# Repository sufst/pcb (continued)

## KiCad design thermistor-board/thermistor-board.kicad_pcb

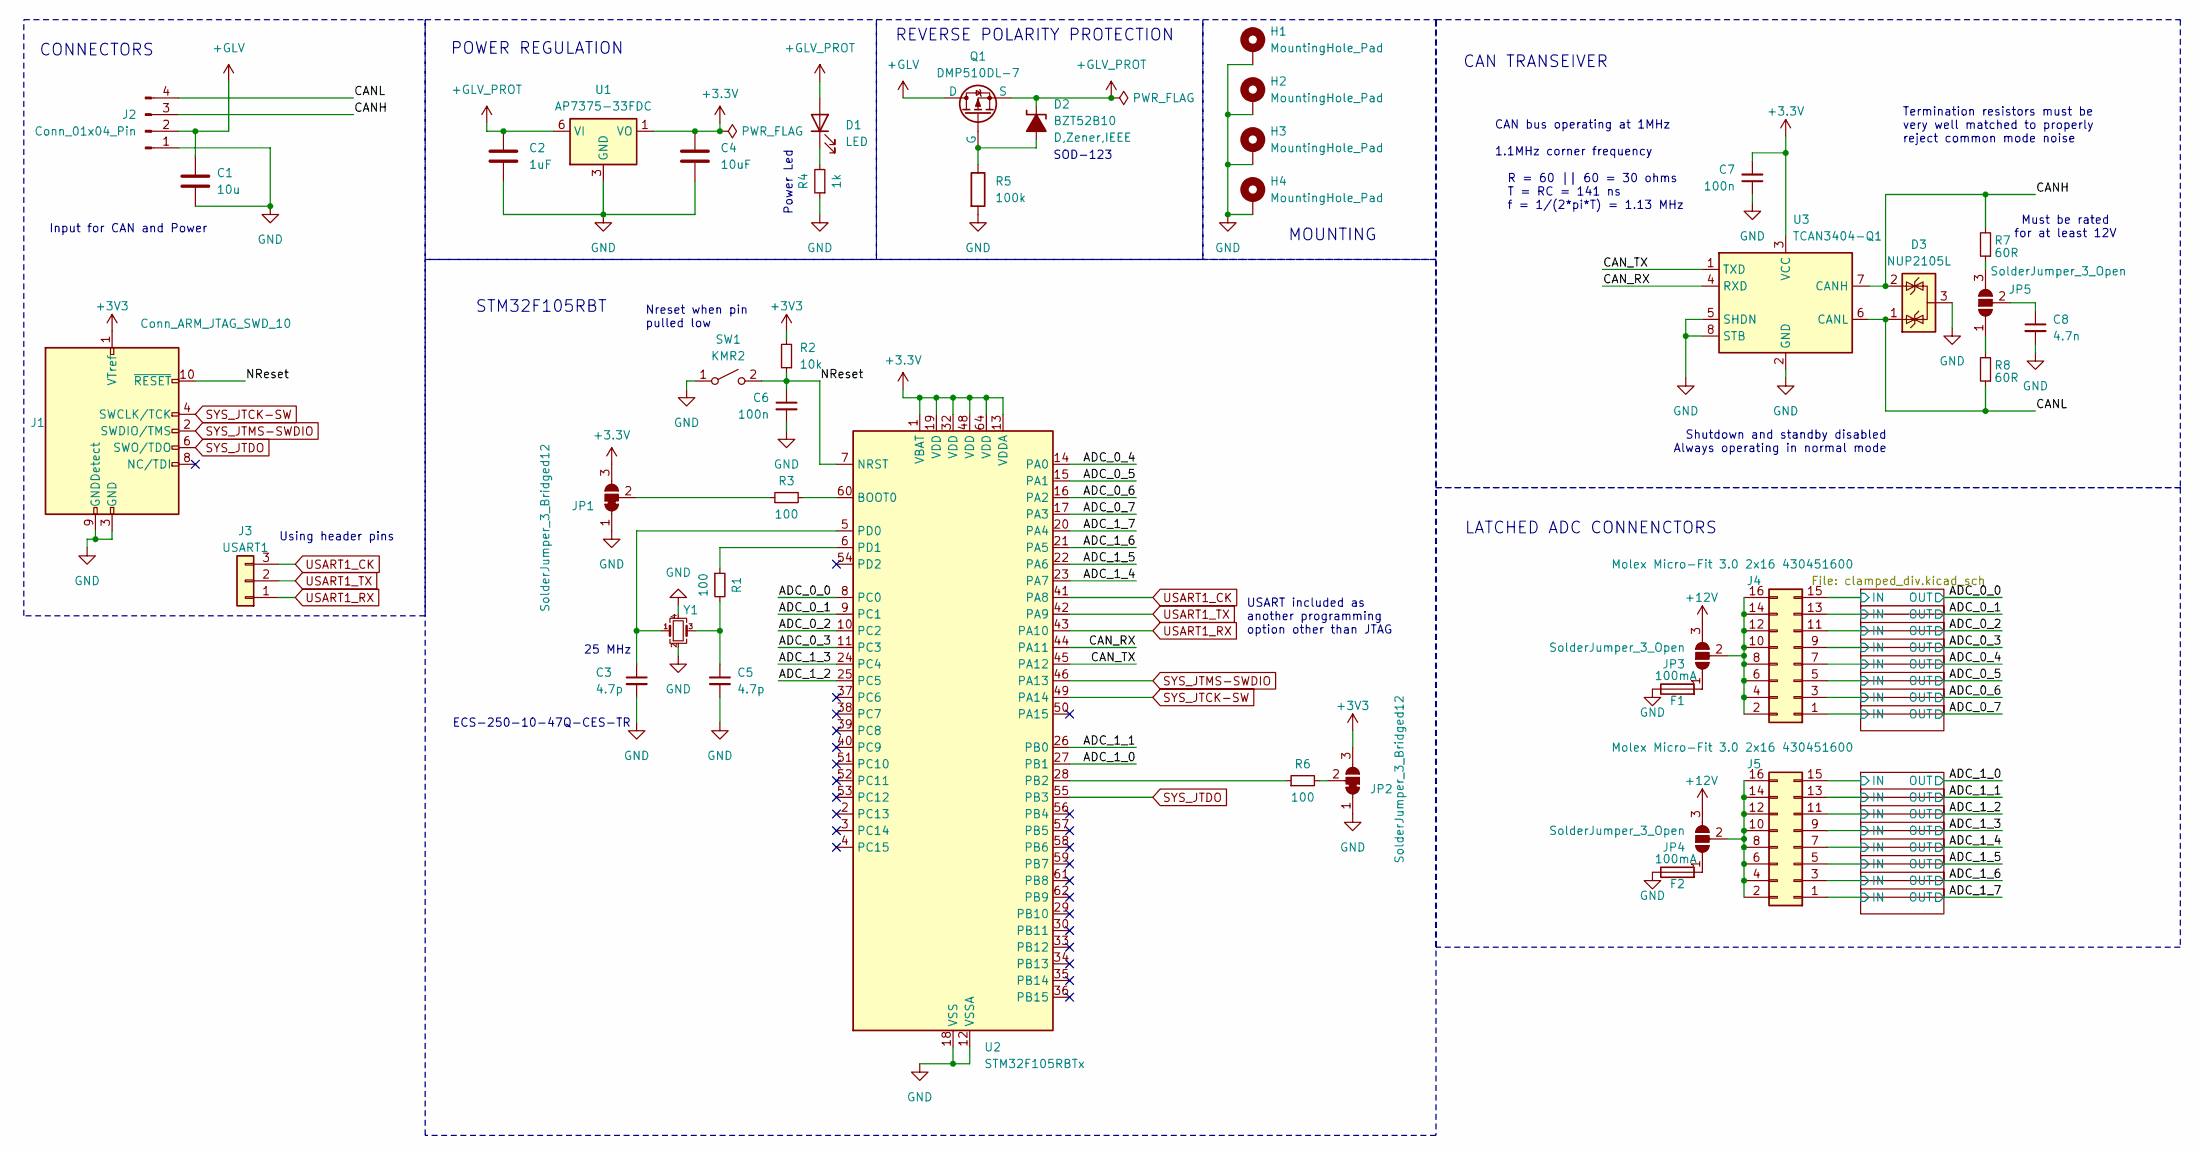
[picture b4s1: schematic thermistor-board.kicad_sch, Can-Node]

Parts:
C1: 10u; C_0805_2012Metric_Pad1.18x1.45mm_HandSolder
C2: 1uF; C_0805_2012Metric_Pad1.18x1.45mm_HandSolder
C3, C5: 4.7p; C_0603_1608Metric_Pad1.08x0.95mm_HandSolder
C4: 10uF; C_0805_2012Metric_Pad1.18x1.45mm_HandSolder
C6, C7: 100n; C_0603_1608Metric_Pad1.08x0.95mm_HandSolder
C8: 4.7n; C_0603_1608Metric_Pad1.08x0.95mm_HandSolder
D1: LED; LED_0805_2012Metric_Pad1.15x1.40mm_HandSolder
D2: BZT52B10; D_SOD-123; MPN BZT52B10
D3: NUP2105L; SOT-23; MPN NUP2105L
F1, F2: 100mA; Fuse_0805_2012Metric_Pad1.15x1.40mm_HandSolder
H1, H2, H3, H4: MountingHole_Pad; MountingHole_3.2mm_M3_Pad_Via
J1: Conn_ARM_JTAG_SWD_10; SHF10501LDSMLC; MPN SHF-105-01-L-D-SM-LC
J2: Conn_01x04_Pin; Molex_Micro-Fit_3.0_43045-0400_2x02_P3.00mm_Horizontal
J3: USART1; PinHeader_1x03_P2.54mm_Vertical
J4, J5: Molex Micro-Fit 3.0 2x16 430451600
JP1, JP2: SolderJumper_3_Bridged12; SolderJumper-3_P1.3mm_Bridged12_RoundedPad1.0x1.5mm
JP3, JP4, JP5: SolderJumper_3_Open; SolderJumper-3_P1.3mm_Open_RoundedPad1.0x1.5mm
Q1: DMP510DL-7; SOT-23; MPN DMP510DL-7
R1, R3, R6: 100; R_0603_1608Metric_Pad0.98x0.95mm_HandSolder
R2: 10k; R_0603_1608Metric_Pad0.98x0.95mm_HandSolder
R4: 1k; R_0603_1608Metric_Pad0.98x0.95mm_HandSolder
R5: 100k; R_0805_2012Metric_Pad1.20x1.40mm_HandSolder
R7, R8: 60R; R_0603_1608Metric_Pad0.98x0.95mm_HandSolder
SW1: KMR2; SW_Push_1P1T_NO_CK_KMR2; MPN KMR221NG LFS
U1: AP7375-33FDC; DFN-6-1EP_2x2mm_P0.65mm_EP1.01x1.7mm
U2: STM32F105RBTx; LQFP-64_10x10mm_P0.5mm
U3: TCAN3404-Q1; SOT-23-8_Handsoldering; MPN TCAN3404DDFRQ1
Y1: ECS-250-10-47Q-CES-TR; Resonator_SMD_ECS_ECX-1247Q_1.6x1.2x0.3mm; MPN ECS-250-10-47Q-CES-TR

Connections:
+3.3V: C4.1, C7.2, JP1.3 (B), U1.1 (VO), U2.1 (VBAT), U2.13 (VDDA), U2.19 (VDD), U2.32 (VDD), U2.48 (VDD), U2.64 (VDD), U3.3 (VCC)
+3V3: J1.1 (VTref), JP2.3 (B), R2.2
+12V: JP3.3 (B), JP4.3 (B)
+GLV: C1.1, J2.2, Q1.1 (D)
+GLV_PROT: C2.1, D1.2 (A), D2.1 (K-), Q1.3 (S), U1.6 (VI)
/ADC_0_0: U2.8 (PC0); also elsewhere on the board
/ADC_0_1: U2.9 (PC1); also elsewhere on the board
/ADC_0_2: U2.10 (PC2); also elsewhere on the board
/ADC_0_3: U2.11 (PC3); also elsewhere on the board
/ADC_0_4: U2.14 (PA0); also elsewhere on the board
/ADC_0_5: U2.15 (PA1); also elsewhere on the board
/ADC_0_6: U2.16 (PA2); also elsewhere on the board
/ADC_0_7: U2.17 (PA3); also elsewhere on the board
/ADC_1_0: U2.27 (PB1); also elsewhere on the board
/ADC_1_1: U2.26 (PB0); also elsewhere on the board
/ADC_1_2: U2.25 (PC5); also elsewhere on the board
/ADC_1_3: U2.24 (PC4); also elsewhere on the board
/ADC_1_4: U2.23 (PA7); also elsewhere on the board
/ADC_1_5: U2.22 (PA6); also elsewhere on the board
/ADC_1_6: U2.21 (PA5); also elsewhere on the board
/ADC_1_7: U2.20 (PA4); also elsewhere on the board
/CANH: D3.2 (K), J2.3, R7.2, U3.7 (CANH)
/CANL: D3.1 (K), J2.4, R8.1, U3.6 (CANL)
/CAN_RX: U2.44 (PA11), U3.4 (RXD)
/CAN_TX: U2.45 (PA12), U3.1 (TXD)
/NReset: C6.1, J1.10 (~RESET), R2.1, SW1.2 (B), U2.7 (NRST)
GND: C1.2, C2.2, C3.2, C4.2, C5.2, C6.2, C7.1, C8.2, D3.3 (A), F1.1, F2.1, H1.1, H2.1, H3.1, H4.1, J1.3 (GND), J1.5 (GND), J1.9 (GNDDetect), J2.1, JP1.1 (A), JP2.1 (A), R4.1, R5.2, SW1.1 (A), U1.3 (GND), U1.7 (GND), U2.12 (VSSA), U2.18 (VSS), U2.31 (VSS), U2.47 (VSS), U2.63 (VSS), U3.2 (GND), U3.5 (SHDN), U3.8 (STB), Y1.2, Y1.4; also elsewhere on the board
unnamed: C5.1, R1.2, Y1.3
unnamed: D1.1 (K), R4.2
unnamed: D2.2 (A+), Q1.2 (G), R5.1
unnamed: J4.2, J4.4, J4.6, J4.8, J4.10, J4.12, J4.14, J4.16, JP3.2 (C)
unnamed: J5.2, J5.4, J5.6, J5.8, J5.10, J5.12, J5.14, J5.16, JP4.2 (C)
unnamed: JP1.2 (C), R3.1
unnamed: JP2.2 (C), R6.2
unnamed: F1.2, JP3.1 (A)
unnamed: F2.2, JP4.1 (A)
unnamed: JP5.1 (A), R8.2
unnamed: JP5.3 (B), R7.1
unnamed: C8.1, JP5.2 (C)
unnamed: R3.2, U2.60 (BOOT0)
unnamed: R6.1, U2.28 (PB2)
unnamed: C3.1, U2.5 (PD0), Y1.1
unnamed: R1.1, U2.6 (PD1)
SYS_JTCK-SW: J1.4 (SWCLK/TCK), U2.49 (PA14)
SYS_JTDO: J1.6 (SWO/TDO), U2.55 (PB3)
SYS_JTMS-SWDIO: J1.2 (SWDIO/TMS), U2.46 (PA13)
USART1_CK: J3.3, U2.41 (PA8)
USART1_RX: J3.1, U2.43 (PA10)
USART1_TX: J3.2, U2.42 (PA9)

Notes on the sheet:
REVERSE POLARITY PROTECTION
Must be rated for at least 12V
25 MHz
STM32F105RBT
LATCHED ADC CONNENCTORS
Input for CAN and Power
CONNECTORS
CAN TRANSEIVER
SOD-123
Nreset when pin pulled low
Shutdown and standby disabled Always operating in normal mode
ECS-250-10-47Q-CES-TR
Power Led
CAN bus operating at 1MHz 1.1MHz corner frequency R = 60 || 60 = 30 ohms T = RC = 141 ns f = 1/(2*pi*T) = 1.13 MHz
POWER REGULATION
Using header pins
Termination resistors must be very well matched to properly reject common mode noise
USART included as another programming option other than JTAG
MOUNTING

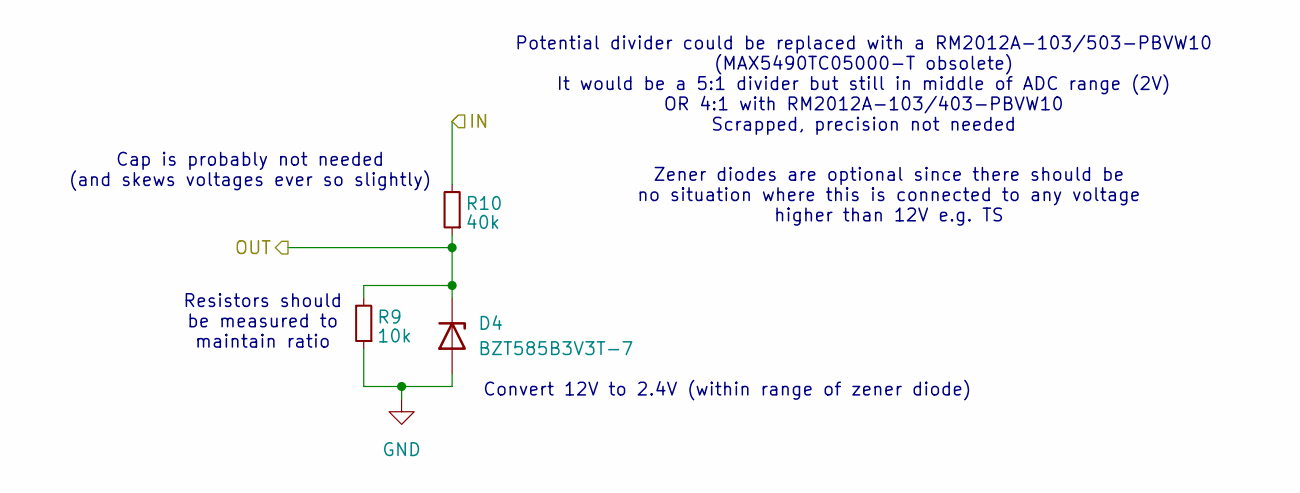
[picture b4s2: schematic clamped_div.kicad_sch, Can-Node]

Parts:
D4: BZT585B3V3T-7; D_SOD-523; Mouser Part Number 621-BZT585B3V3T-7
R9: 10k; R_0805_2012Metric_Pad1.20x1.40mm_HandSolder; Manufacturer_Part_Number CRGH0805F12R; Mouser Part Number 279-CRGH0805F12R
R10: 40k; R_0805_2012Metric_Pad1.20x1.40mm_HandSolder; Manufacturer_Part_Number CRCW080540K0FKEA; Mouser Part Number 71-CRCW080540K0FKEA

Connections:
/ADC_1_7: D4.1 (K), R9.2, R10.1; also elsewhere on the board
/ClampedDivider15/IN: R10.2
GND: D4.2 (A), R9.1; also elsewhere on the board

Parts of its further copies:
D5, D6, D7, D8, D9, D10, D11, D12, D13, D14, D15, D16, D17, D18, D19: BZT585B3V3T-7; D_SOD-523; Mouser Part Number 621-BZT585B3V3T-7
R11, R13, R15, R17, R19, R21, R23, R25, R27, R29, R31, R33, R35, R37, R39: 10k; R_0805_2012Metric_Pad1.20x1.40mm_HandSolder; Manufacturer_Part_Number CRGH0805F12R; Mouser Part Number 279-CRGH0805F12R
R12, R14, R16, R18, R20, R22, R24, R26, R28, R30, R32, R34, R36, R38, R40: 40k; R_0805_2012Metric_Pad1.20x1.40mm_HandSolder; Manufacturer_Part_Number CRCW080540K0FKEA; Mouser Part Number 71-CRCW080540K0FKEA

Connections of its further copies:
/ADC_0_0: D5.1 (K), R11.2, R12.1; also elsewhere on the board
/ADC_0_1: D17.1 (K), R35.2, R36.1; also elsewhere on the board
/ADC_0_2: D19.1 (K), R39.2, R40.1; also elsewhere on the board
/ADC_0_3: D18.1 (K), R37.2, R38.1; also elsewhere on the board
/ADC_0_4: D16.1 (K), R33.2, R34.1; also elsewhere on the board
/ADC_0_5: D15.1 (K), R31.2, R32.1; also elsewhere on the board
/ADC_0_6: D14.1 (K), R29.2, R30.1; also elsewhere on the board
/ADC_0_7: D13.1 (K), R27.2, R28.1; also elsewhere on the board
/ADC_1_0: D12.1 (K), R25.2, R26.1; also elsewhere on the board
/ADC_1_1: D11.1 (K), R23.2, R24.1; also elsewhere on the board
/ADC_1_2: D10.1 (K), R21.2, R22.1; also elsewhere on the board
/ADC_1_3: D9.1 (K), R19.2, R20.1; also elsewhere on the board
/ADC_1_4: D8.1 (K), R17.2, R18.1; also elsewhere on the board
/ADC_1_5: D7.1 (K), R15.2, R16.1; also elsewhere on the board
/ADC_1_6: D6.1 (K), R13.2, R14.1; also elsewhere on the board
/ClampedDivider16/IN: R12.2
/ClampedDivider17/IN: R14.2
/ClampedDivider18/IN: R16.2
/ClampedDivider19/IN: R18.2
/ClampedDivider20/IN: R20.2
/ClampedDivider21/IN: R22.2
/ClampedDivider22/IN: R24.2
/ClampedDivider23/IN: R26.2
/ClampedDivider24/IN: R28.2
/ClampedDivider25/IN: R30.2
/ClampedDivider26/IN: R32.2
/ClampedDivider27/IN: R34.2
/ClampedDivider28/IN: R36.2
/ClampedDivider29/IN: R38.2
/ClampedDivider30/IN: R40.2
GND: D5.2 (A), D6.2 (A), D7.2 (A), D8.2 (A), D9.2 (A), D10.2 (A), D11.2 (A), D12.2 (A), D13.2 (A), D14.2 (A), D15.2 (A), D16.2 (A), D17.2 (A), D18.2 (A), D19.2 (A), R11.1, R13.1, R15.1, R17.1, R19.1, R21.1, R23.1, R25.1, R27.1, R29.1, R31.1, R33.1, R35.1, R37.1, R39.1; also elsewhere on the board

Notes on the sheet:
Cap is probably not needed (and skews voltages ever so slightly)
Convert 12V to 2.4V (within range of zener diode)
Zener diodes are optional since there should be no situation where this is connected to any voltage higher than 12V e.g. TS
Resistors should be measured to maintain ratio
Potential divider could be replaced with a RM2012A-103/503-PBVW10 (MAX5490TC05000-T obsolete) It would be a 5:1 divider but still in middle of ADC range (2V) OR 4:1 with RM2012A-103/403-PBVW10 Scrapped, precision not needed

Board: 4 copper layers, 85 parts (0 on the bottom side), 44 nets, no tracks yet.

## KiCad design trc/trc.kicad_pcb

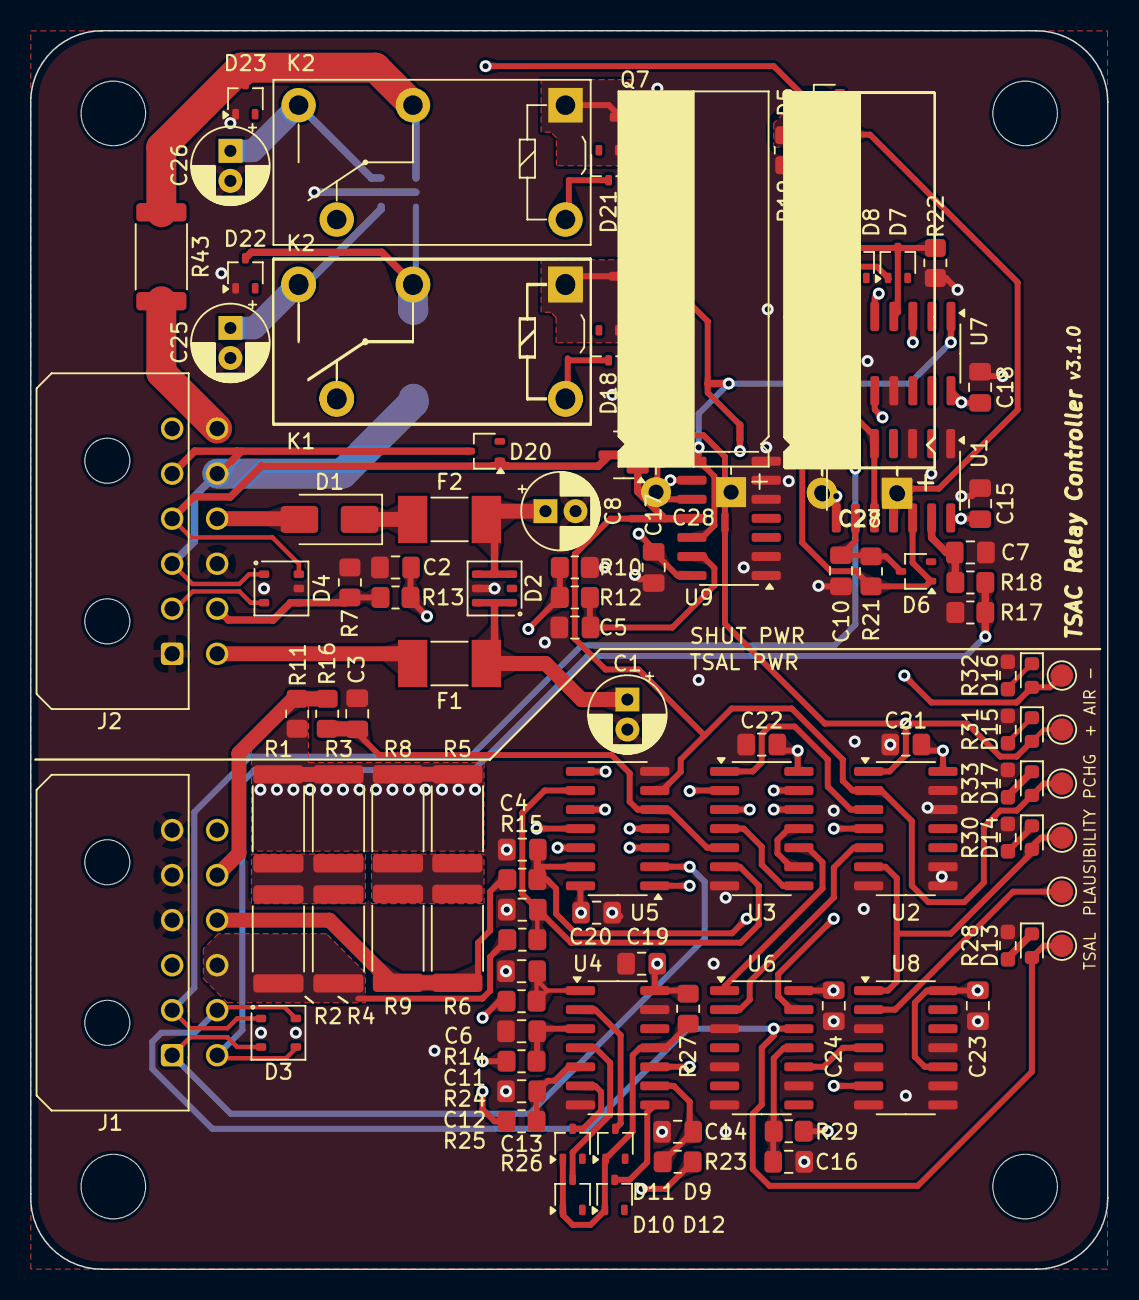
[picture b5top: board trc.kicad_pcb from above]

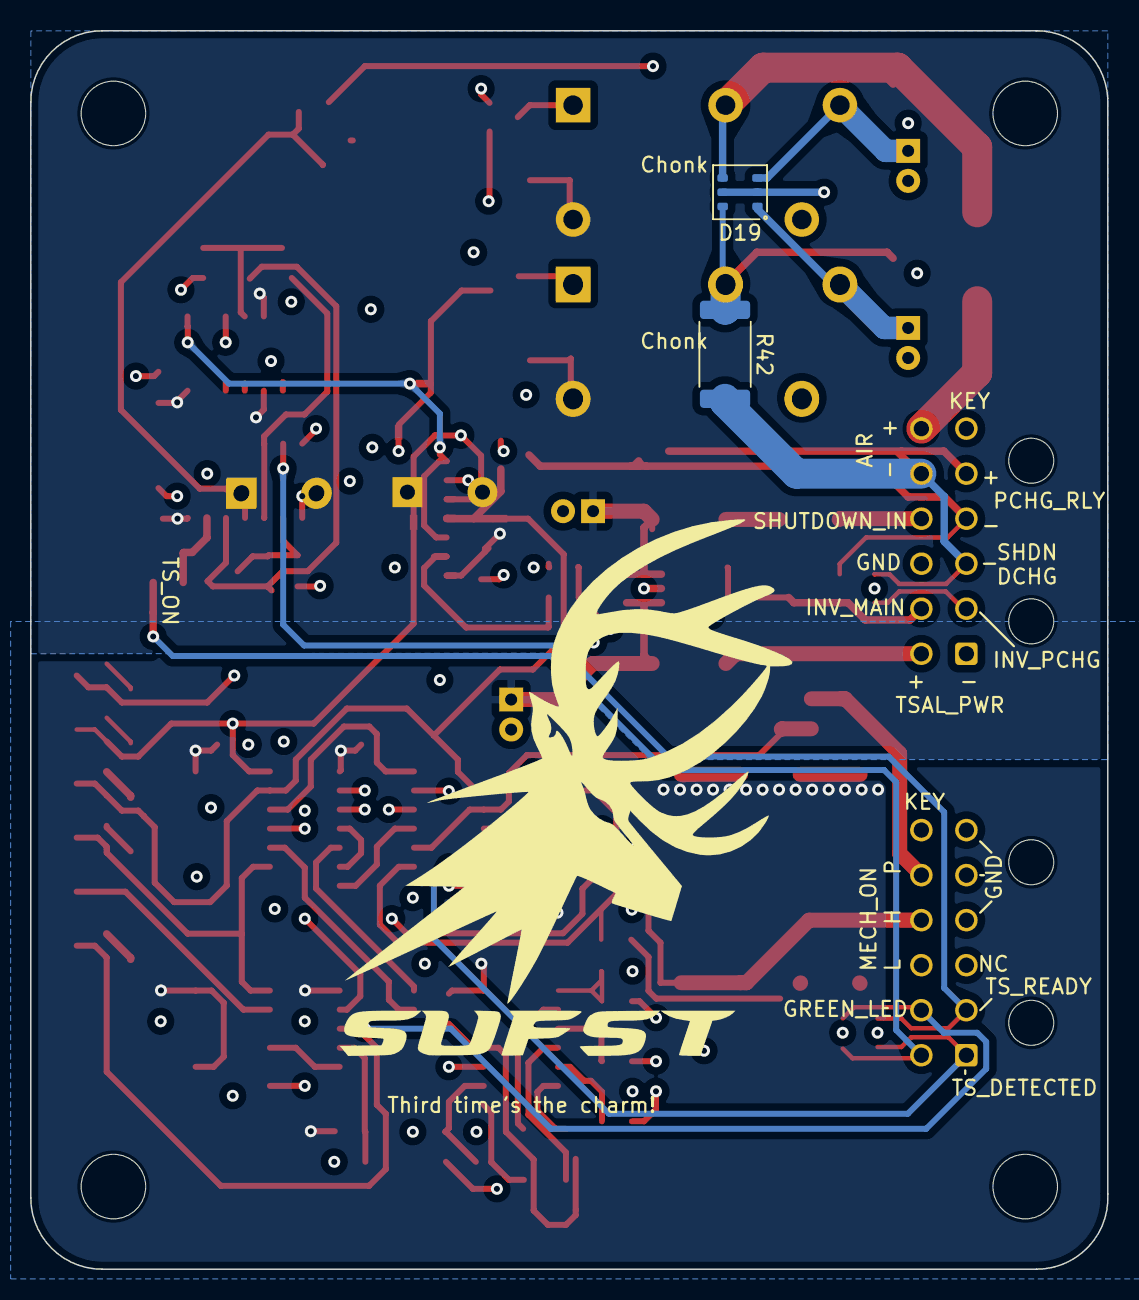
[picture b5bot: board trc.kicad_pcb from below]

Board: 6 copper layers, 71.8 x 82.5 mm, 120 parts (2 on the bottom side), 73 nets.

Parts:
C1, C8, C25, C26: 100u; CP_Radial_D5.0mm_P2.00mm
C2, C3, C4, C5, C6, C7, C15, C17, C18, C19, C20, C21, C22, C23, C24: 100n; C_0805_2012Metric_Pad1.18x1.45mm_HandSolder
C9, C11, C12, C13, C14, C16: 10u; C_0805_2012Metric_Pad1.18x1.45mm_HandSolder
C10: 1u; C_0805_2012Metric_Pad1.18x1.45mm_HandSolder
C27, C28, C28#2: 2200u; CP_Radial_D10.0mm_P5.00mm_H25mm_Horizontal1
D1: SS14+; D_SMA
D2, D3, D4, D19: PESD12VS5UD; TSOP-6_1.65x3.05mm_P0.95mm
D5, D6, D7, D8, D9, D10, D11, D12, D18, D20, D21, D22, D23: BAT54W; SOT-323_SC-70
D13: GREEN; LED_0603_1608Metric
D14: RED; LED_0603_1608Metric
D15: BLUE; LED_0603_1608Metric
D16: YELLOW; LED_0603_1608Metric
D17: ORANGE; LED_0603_1608Metric
F1, F2: 0448.500MR; Fuse_Littelfuse-NANO2-451_453
GRN1: TestPoint; TestPoint_Pad_D1.5mm
H1, H2, H3, H4: MountingHole; MountingHole_4.3mm_M4
IMP1: TestPoint; TestPoint_Pad_D1.5mm
J1, J2: Molex 43045-1200; Molex_Micro-Fit_3.0_43045-1200_2x06_P3.00mm_Horizontal
K1, K2, K2#2: G5Q-1A-EU DC12; Relay_SPDT_Omron-G5Q-1
NT1, NT2, NT3, NT4, NT5: NetTie_2; NetTie-2_SMD_Pad0.5mm
Q3, Q4, Q7: XP262N7002TR-G; SOT-23
R1, R2, R3, R4, R5, R6, R8, R9: 270; R_2512_6332Metric
R7, R10, R11, R12, R13, R14, R15, R16, R17, R18, R22, R24, R25, R26, R27, R29: 10k; R_0805_2012Metric_Pad1.20x1.40mm_HandSolder
R19: 1k; R_0805_2012Metric_Pad1.20x1.40mm_HandSolder
R20: 47k; R_0805_2012Metric_Pad1.20x1.40mm_HandSolder
R21, R23: 100k; R_0805_2012Metric_Pad1.20x1.40mm_HandSolder
R28, R30, R31, R32, R33: 10k; R_0603_1608Metric_Pad0.98x0.95mm_HandSolder
R42, R43: 10; R_2512_6332Metric
TP1: +AIR_INTENDED; TestPoint_Pad_D1.5mm
TP2: -AIR_INTENDED; TestPoint_Pad_D1.5mm
TP3: PRCHG_INTENDED; TestPoint_Pad_D1.5mm
U1, U4, U6: 40106; SOIC-14_3.9x8.7mm_P1.27mm
U2: 4071; SOIC-14_3.9x8.7mm_P1.27mm
U3, U5, U9: 4081; SOIC-14_3.9x8.7mm_P1.27mm
U7, U8: 4013; SOIC-14_3.9x8.7mm_P1.27mm

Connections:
+12V: C8.1, C15.2, C17.2, C18.2, D2.3 (L2), D2.4 (L3), D18.3 (K), D21.3 (K), F2.2, K2#2.5, U1.14 (VDD), U7.5 (D), U7.10 (R), U7.14 (VDD), U9.14 (VDD)
+12VT: C1.1, C19.2, C20.2, C21.2, C22.2, C23.2, C24.2, D2.1 (L1), D2.6 (L4), F1.2, R1.1, R3.1, R5.1, R8.1, R11.1, R27.2, R29.2, U2.14 (VDD), U3.14 (VDD), U4.14 (VDD), U5.14 (VDD), U6.14 (VDD), U8.10 (R), U8.14 (VDD)
/CLOSE_NEG_AIR: NT1.2, NT3.2, Q3.1 (G)
/CLOSE_PCHG_RLY: NT4.2, Q4.1 (G), U9.11
/CLOSE_POS_AIR: NT2.2, Q7.1 (G), U9.10
/Control Logic/+AIR_MECH_IMP: R26.1, U5.11
/Control Logic/+AIR_MECH_IMP_RC: C13.1, R26.2, U4.5
/Control Logic/-AIR_MECH_IMP: R25.1, U5.10
/Control Logic/-AIR_MECH_IMP_RC: C12.1, R25.2, U4.3
/Control Logic/AIRS_CLSD: U3.3, U5.1
/Control Logic/HIGH_AIR_INTENDED_ON: D15.2 (A), NT2.1, TP1.1, U2.1, U5.12
/Control Logic/HS_ACTIVE: U2.3, U3.1
/Control Logic/HV_IMP: R23.1, U5.3
/Control Logic/HV_IMP_RC: C14.1, R23.2, U4.9
/Control Logic/IMPLAUSIBLE: D14.2 (A), IMP1.1, U2.6, U8.1 (Q)
/Control Logic/IMP_TRIG: U4.10, U8.6 (S)
/Control Logic/INV_CLOSE_MAIN_CONTACTOR: C2.2, R13.2, U9.9
/Control Logic/INV_CLOSE_PCHG_RLY: C5.2, R12.2, U9.13
/Control Logic/LOW_AIR_INTENDED_ON: D16.2 (A), NT3.1, TP2.1, U3.2, U5.8
/Control Logic/POR: D8.1 (A), U1.5, U1.10
/Control Logic/POR_RC: C9.1, D5.1 (A), R20.1, U1.11
/Control Logic/PRCHG_INTENDED_ON: D17.2 (A), NT4.1, TP3.1, U2.2, U5.6
/Control Logic/PRCHG_MECH_IMP: R24.1, U5.4
/Control Logic/PRCHG_MECH_IMP_RC: C11.1, R24.2, U4.1
/Control Logic/TSAL_POR: U6.10, U8.4 (R)
/Control Logic/TSAL_POR_RC: C16.1, R29.1, U6.11
/Control Logic/TS_ENABLED: NT1.1, U7.1 (Q), U9.8, U9.12
/Control Logic/TS_EN_POR: D7.3 (K), D8.3 (K), R22.1, U7.4 (R)
/Control Logic/TS_EN_RISING: U1.8, U7.3 (C)
/Control Logic/TS_OFF: U3.10, U6.1
/Control Logic/TS_ON_INPUT: C7.1, R18.1, U1.13
/Control Logic/TS_ON_RC: C10.1, D6.3 (K), R21.1, U1.9
/Control Logic/TS_UNSAFE: U2.5, U6.2
/Control Logic/~+AIR_MECH_HV: U3.9, U3.11
/Control Logic/~+AIR_MECH_IMP: D11.3 (K), U4.6
/Control Logic/~-AIR_MECH_IMP: D10.3 (K), U4.4
/Control Logic/~-AIR_PRCHG_MECH: U3.4, U3.8
/Control Logic/~-PRCHG_MECH_IMP: D9.3 (K), U4.2
/Control Logic/~HV_IMP: D12.3 (K), U4.8
/Control Logic/~IMP_TRIG: D9.1 (A), D10.1 (A), D11.1 (A), D12.1 (A), R27.1, U4.11
/Control Logic/~TSAL_IMP: U2.4, U6.13
/Control Logic/~TS_ON: D6.1 (A), D7.1 (A), R21.2, U1.12
/GREEN_LED_ON: D3.6 (L4), D13.2 (A), GRN1.1, J1.8, U6.12
/INV_CLOSE_MAIN_CONTACTOR: D4.4 (L3), J2.8, R7.1, R13.1
/INV_CLOSE_PCHG_RLY: D4.3 (L2), J2.2, R10.1, R12.1
/NEG_AIR: C27.1, D4.1 (L1), J2.3, J2.11, NT5.2, R42.2
/PCHG_RLY+: D20.3 (K), J2.5, NT5.1
/PCHG_RLY-: D4.6 (L4), D20.1 (A), J2.4, Q4.3 (D)
/POS_AIR: C28#2.1, J2.12, R43.2
/Relays/+AIR_OUT: D19.4 (L3), D23.3 (K), K2#2.2, R43.1
/Relays/-AIR_OUT: C26.1, D19.3 (L2), D19.6 (L4), D22.3 (K), K2#2.3, R42.1
/Relays/NEG_AIR_RELAY: D18.1 (A), Q3.3 (D)
/Relays/POS_AIR_RELAY: D21.1 (A), K2#2.1, Q7.3 (D)
/SHDN_IN: C25.1, D1.2 (A), D5.3 (K), D19.1 (L1), J2.10, R19.1, R20.2
/TSAL_POWER: F1.1, J2.7
/TS_ON_INPUT: D3.4 (L3), J1.7, R17.1, R18.2
/TS_READY: D3.1 (L1), J1.2, U1.6
/~HIGH_AIR_MECH_ON_IN: J1.10, R6.2, R9.2, R15.2
/~HIGH_AIR_MECH_ON: C4.1, R15.1, U3.12, U5.13
/~LOW_AIR_MECH_ON_IN: J1.9, R2.2, R4.2, R14.2
/~LOW_AIR_MECH_ON: C6.1, R14.1, U3.6, U5.9
/~PRCHG_MECH_ON_IN: J1.11, R11.2, R16.2
/~PRCHG_MECH_ON: C3.1, R16.1, U3.5, U5.5
/~TS.DETECTED: D3.3 (L2), J1.1, U3.13, U5.2
GND: C1.2, C2.1, C3.2, C4.2, C5.1, C6.2, C7.2, C8.2, C9.2, C10.2, C11.2, C12.2, C13.2, C14.2, C15.1, C16.2, C17.1, C18.1, C19.1, C20.1, C21.1, C22.1, C23.1, C24.1, C25.2, C26.2, C27.2, C28#2.2, D2.5 (VN), D3.2 (VN), D3.5 (VN), D4.2 (VN), D4.5 (VN), D19.2 (VN), D19.5 (VN), D22.1 (A), D23.1 (A), J1.4, J1.5, J1.6, J2.1, J2.9, Q3.2 (S), Q4.2 (S), Q7.2 (S), R7.2, R10.2, R17.2, R19.2, R22.2, R28.2, R30.2, R31.2, R32.2, R33.2, U1.1, U1.3, U1.7 (VSS), U2.7 (VSS), U2.8, U2.9, U2.12, U2.13, U3.7 (VSS), U4.7 (VSS), U4.13, U5.7 (VSS), U6.3, U6.5, U6.7 (VSS), U6.9, U7.6 (S), U7.7 (VSS), U7.8 (S), U7.9 (D), U7.11 (C), U8.3 (C), U8.5 (D), U8.7 (VSS), U8.8 (S), U8.9 (D), U8.11 (C), U9.1, U9.2, U9.5, U9.6, U9.7 (VSS)
unnamed: D1.1 (K), F2.1
unnamed: D13.1 (K), R28.1
unnamed: D14.1 (K), R30.1
unnamed: D15.1 (K), R31.1
unnamed: D16.1 (K), R32.1
unnamed: D17.1 (K), R33.1
unnamed: R1.2, R2.1, R3.2, R4.1
unnamed: R5.2, R6.1, R8.2, R9.1

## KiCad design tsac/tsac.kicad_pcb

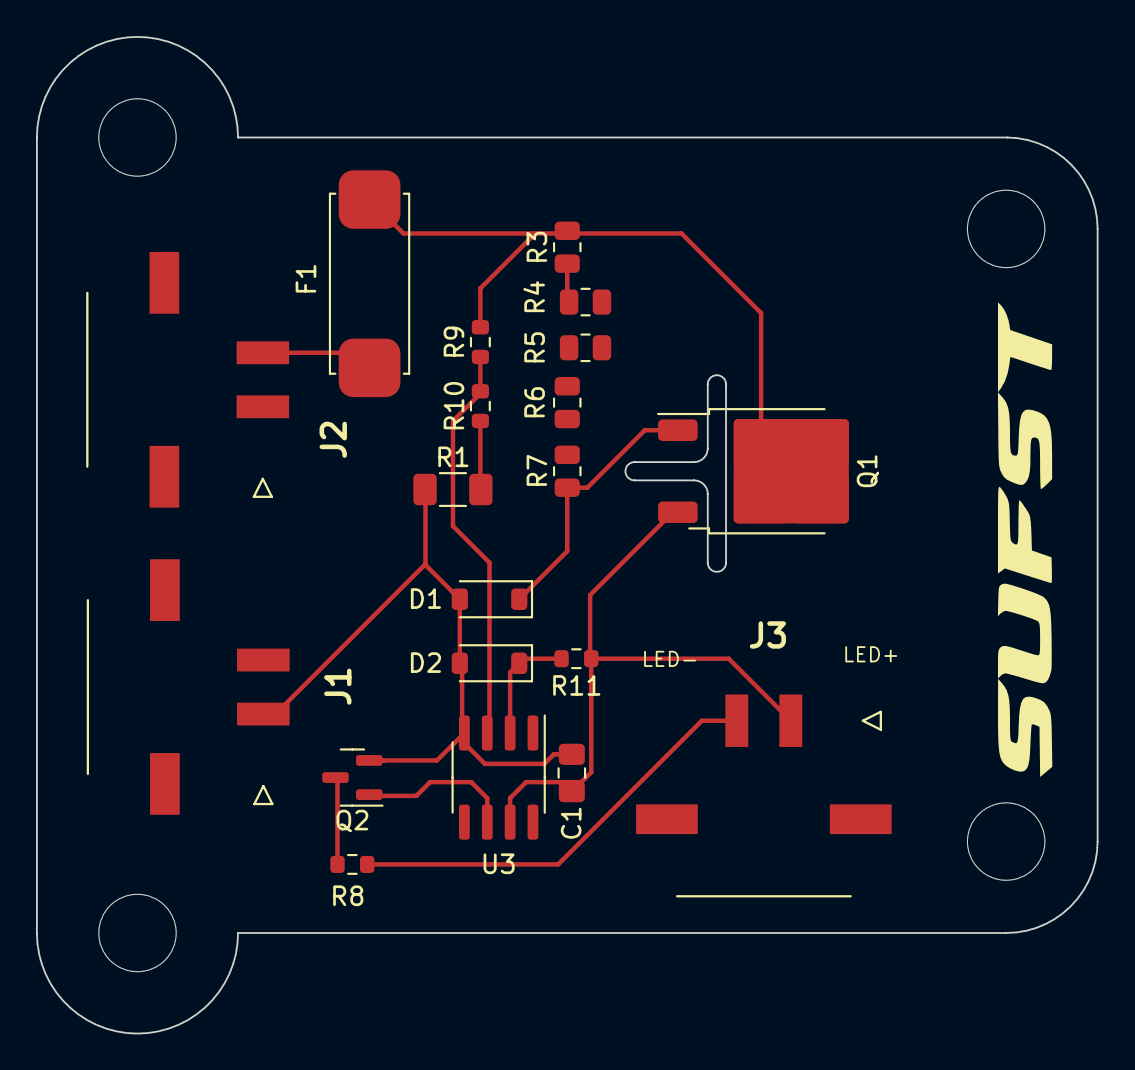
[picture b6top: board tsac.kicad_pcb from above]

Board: 2 copper layers, 58.9 x 55.4 mm, 24 parts (0 on the bottom side), 14 nets.

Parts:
C1: 100n; C_0805_2012Metric_Pad1.18x1.45mm_HandSolder
D1: MMSZ4699T1G; D_SOD-123
D2: MMSZ4691T1G; D_SOD-123
F1: 0461.500ER; Littelfuse-04611-25ER
H1, H2, H3, H4: MountingHole; MountingHole_4.3mm_M4
J1: TS HV-; 43650-02_12,13,14_
J2: TS HV+; 43650-02_12,13,14_
J3: LED; 43650-02_12,13,14_
Q1: FQD1N80TM; TO-252-2
Q2: XP262N7002TR-G; SOT-23
R1: 0; R_1206_3216Metric_Pad1.30x1.75mm_HandSolder
R3, R4, R5, R6, R7: 200k; R_0805_2012Metric
R8: 470; R_0603_1608Metric
R9: 900k; R_0603_1608Metric
R10: 110k; R_0603_1608Metric
R11: 4.7k; R_0603_1608Metric
U3: OP777; SOIC-8_3.9x4.9mm_P1.27mm

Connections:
unnamed: D1.1 (A1), Q1.1 (G), R7.1
unnamed: C1.2, D1.2 (A2), D2.2 (A2), J1.1, Q2.2 (S), R1.1, R1.2, R10.1, U3.4 (V-)
unnamed: D2.1 (A1), R11.1, U3.2 (-)
unnamed: F1.2, J2.2
unnamed: C1.1, J3.1, Q1.3 (S), R11.2, U3.7 (V+)
unnamed: J3.2, R8.2
unnamed: F1.1, Q1.2 (D), R3.2, R9.2
unnamed: Q2.3 (D), R8.1
unnamed: Q2.1 (G), U3.6
unnamed: R3.1, R4.1
unnamed: R4.2, R5.2
unnamed: R5.1, R6.1
unnamed: R6.2, R7.2
unnamed: R9.1, R10.2, U3.3 (+)

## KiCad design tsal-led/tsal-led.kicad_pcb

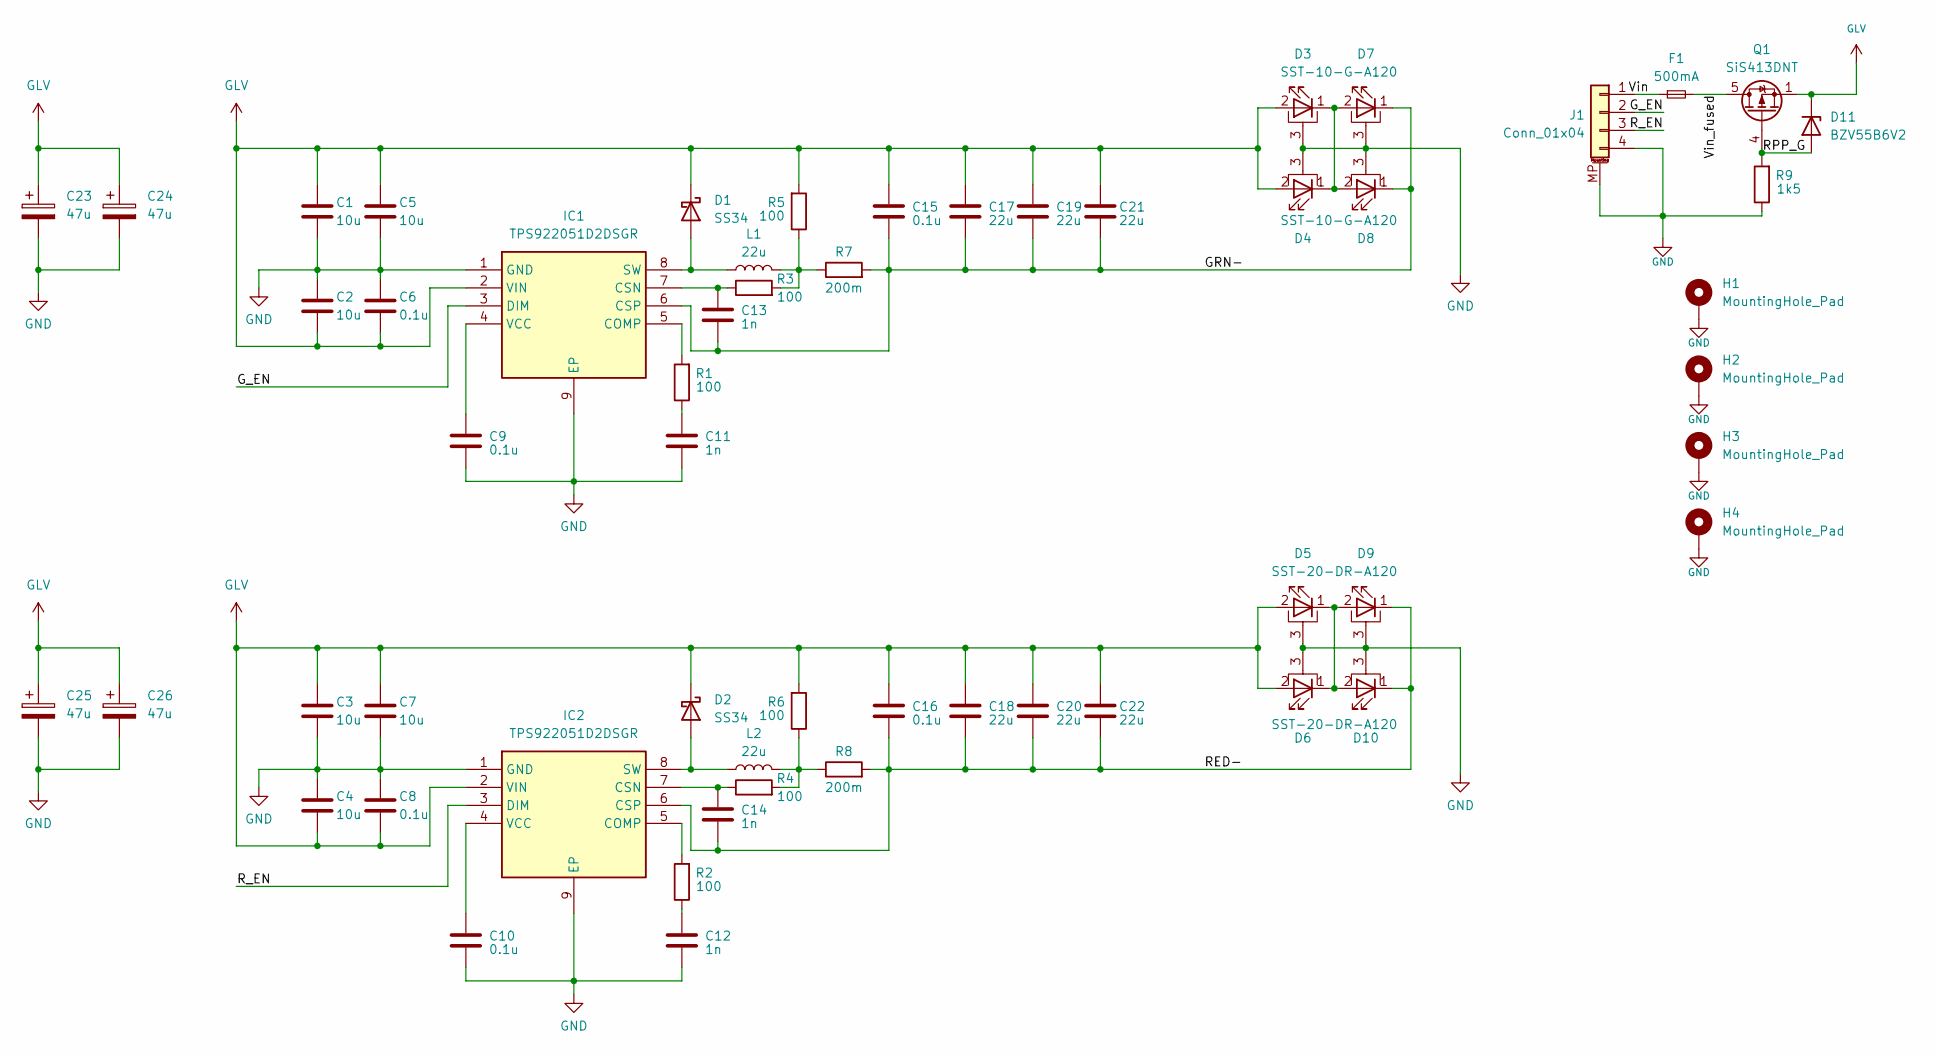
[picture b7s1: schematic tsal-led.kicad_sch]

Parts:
C1, C2, C3, C4, C5, C7: 10u; C_0603_1608Metric
C6, C8, C9, C10, C15, C16: 0.1u; C_0603_1608Metric
C11, C12, C13, C14: 1n; C_0603_1608Metric
C17, C18, C19, C20, C21, C22: 22u; C_0805_2012Metric
C23, C24, C25, C26: 47u; CP_Elec_6.3x7.7
D1, D2: SS34; D_SMA
D3, D4, D7, D8: SST-10-G-A120; Luminus_SST10_20_3030_pad
D5, D6, D9, D10: SST-20-DR-A120; Luminus_SST10_20_3030_pad
D11: BZV55B6V2; D_MiniMELF
F1: 500mA; Fuse_0603_1608Metric
H1, H2, H3, H4: MountingHole_Pad; MountingHole_3mm_Pad_Via
IC1, IC2: TPS922051D2DSGR; Texas_DSG0008A_WSON-8-1EP_2x2mm_P0.5mm_EP0.9x1.6mm; Manufacturer_Part_Number TPS922051D2DSGR
J1: Conn_01x04; Molex_Micro-Fit_3.0_43650-0410_1x04-1MP_P3.00mm_Horizontal
L1, L2: 22u; L_Coilcraft_XAL5050-XXX
Q1: SiS413DNT; Vishay_PowerPAK_1212-8_Single
R1, R2, R3, R4, R5, R6: 100; R_0603_1608Metric
R7, R8: 200m; R_1206_3216Metric
R9: 1k5; R_0603_1608Metric

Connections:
/GRN-: C13.2, C15.2, C17.2, C19.2, C21.2, D7.1 (K), D8.1 (K), IC1.6 (CSP), R7.2
/G_EN: IC1.3 (DIM), J1.2
/RED-: C14.2, C16.2, C18.2, C20.2, C22.2, D9.1 (K), D10.1 (K), IC2.6 (CSP), R8.2
/RPP_G: D11.2 (A), Q1.4 (G), R9.2
/R_EN: IC2.3 (DIM), J1.3
/Vin: F1.1, J1.1
/Vin_fused: F1.2, Q1.5 (D)
GLV: C1.1, C2.2, C3.1, C4.2, C5.1, C6.2, C7.1, C8.2, C15.1, C16.1, C17.1, C18.1, C19.1, C20.1, C21.1, C22.1, C23.1, C24.1, C25.1, C26.1, D1.1 (K), D2.1 (K), D3.2 (A), D4.2 (A), D5.2 (A), D6.2 (A), D11.1 (K), IC1.2 (VIN), IC2.2 (VIN), Q1.1 (S), Q1.2 (S), Q1.3 (S), R5.2, R6.2
GND: C1.2, C2.1, C3.2, C4.1, C5.2, C6.1, C7.2, C8.1, C9.2, C10.2, C11.2, C12.2, C23.2, C24.2, C25.2, C26.2, D3.3 (PAD), D4.3 (PAD), D5.3 (PAD), D6.3 (PAD), D7.3 (PAD), D8.3 (PAD), D9.3 (PAD), D10.3 (PAD), H1.1, H2.1, H3.1, H4.1, IC1.1 (GND), IC1.9 (EP), IC2.1 (GND), IC2.9 (EP), J1.4, J1.MP (MountPin), R9.1
unnamed: C11.1, R1.1
unnamed: C12.1, R2.1
unnamed: D1.2 (A), IC1.8 (SW), L1.1
unnamed: D2.2 (A), IC2.8 (SW), L2.1
unnamed: D3.1 (K), D4.1 (K), D7.2 (A), D8.2 (A)
unnamed: D5.1 (K), D6.1 (K), D9.2 (A), D10.2 (A)
unnamed: IC1.5 (COMP), R1.2
unnamed: C13.1, IC1.7 (CSN), R3.1
unnamed: C9.1, IC1.4 (VCC)
unnamed: IC2.5 (COMP), R2.2
unnamed: C14.1, IC2.7 (CSN), R4.1
unnamed: C10.1, IC2.4 (VCC)
unnamed: L1.2, R3.2, R5.1, R7.1
unnamed: L2.2, R4.2, R6.1, R8.1

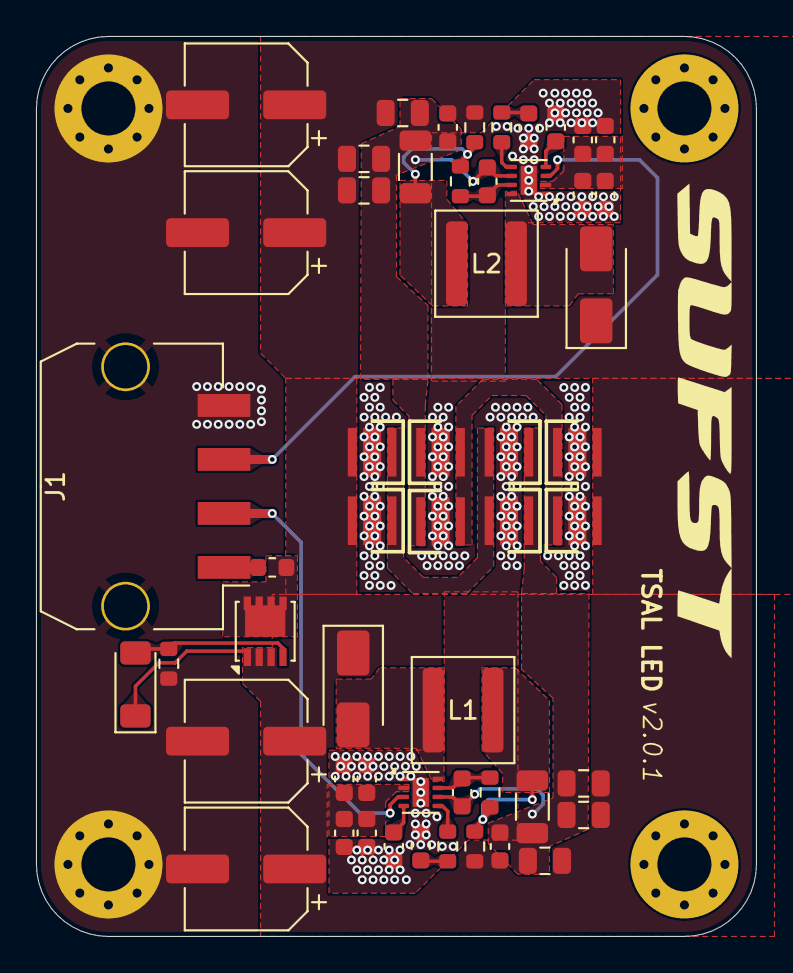
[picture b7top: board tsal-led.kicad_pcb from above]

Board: 4 copper layers, 40.0 x 50.0 mm, 57 parts (0 on the bottom side), 23 nets.
